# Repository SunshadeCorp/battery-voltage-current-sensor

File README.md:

# battery-voltage-current-sensor
Sensor Board for a voltage and current measurement

D1 Mini ESP8266 Microcontroller

Umax: 750VDC

Imax: +-50A 

Integrated supply voltage generation from the highvoltage source

2x temperature sensors onboard for system monitoring and overload protection

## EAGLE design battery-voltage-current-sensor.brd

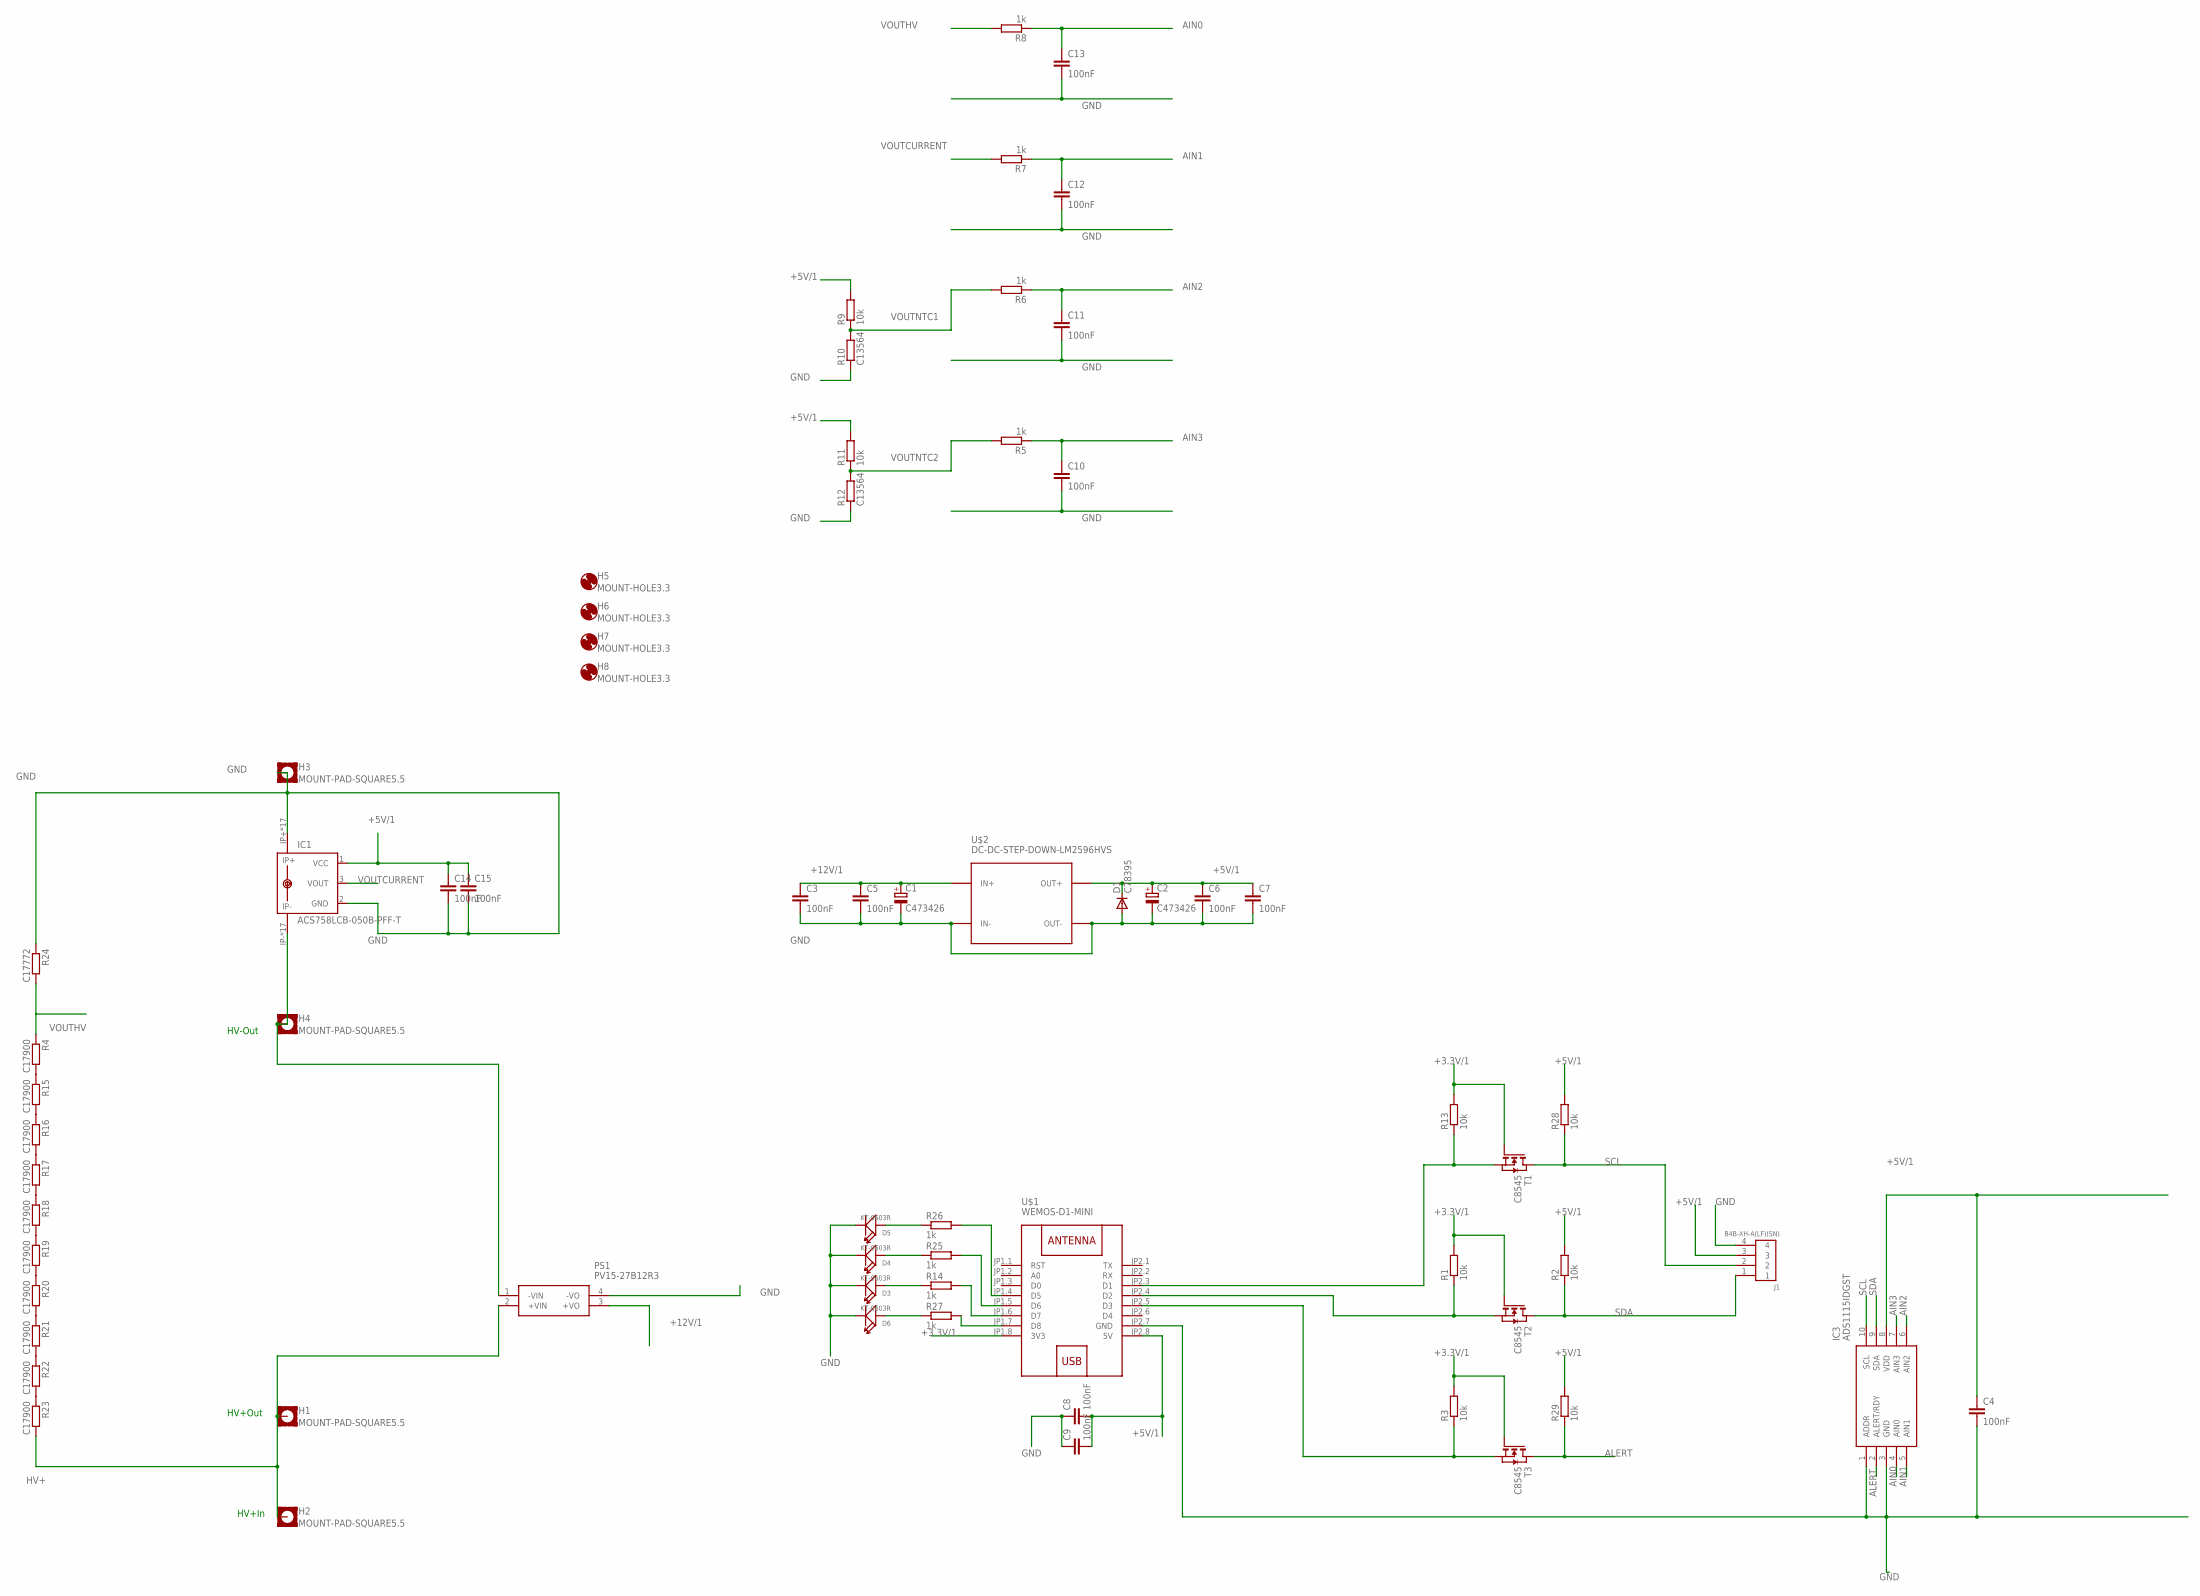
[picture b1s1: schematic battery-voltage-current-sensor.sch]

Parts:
C1, C2: C473426; UD-6,3X7,7_NICHICON
C3, C5, C6, C7, C8, C9, C10, C11, C12, C13, C14, C15: 100nF; C0603
C4: 100nF; C0805
D1: C78395; SMB
D3, D4, D5, D6: KT-0603R; LED-0603
H1, H2, H3, H4: MOUNT-PAD-SQUARE5.5; 5,5-PAD-SQUARE
H5, H6, H7, H8: MOUNT-HOLE3.3; 3,3
IC1: ACS758LCB-050B-PFF-T; CB-PFF
IC3: ADS1115IDGST; SOP50P490X110-10N
J1: B4B-XH-A(LF)(SN)
PS1: PV15-27B12R3; PV1527B12R3
R1, R2, R3, R9, R11, R13, R28, R29: 10k; R0603
R4, R15, R16, R17, R18, R19, R20, R21, R22, R23: C17900; R1206
R5, R6, R7, R8, R14, R25, R26, R27: 1k; R0805
R10, R12: C13564; R0603
R24: C17772; R0805
T1, T2, T3: C8545; SOT-23
U$1: WEMOS-D1-MINI
U$2: DC-DC-STEP-DOWN-LM2596HVS

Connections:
+3.3V/1: R1.2, R3.2, R13.2, T1.3 (G), T2.3 (G), T3.3 (G), U$1.JP1.8 (3V3)
+5V/1: C2.+, C4.1, C6.1, C7.1, C8.2, C9.2, C14.1, C15.1, D1.C, IC1.1 (VCC), IC3.8 (VDD), J1.3, R2.2, R9.2, R11.2, R28.2, R29.2, U$1.JP2.8 (5V), U$2.OUT+
+12V/1: C1.+, C3.1, C5.1, PS1.3 (+VO), U$2.IN+
AIN0: C13.1, IC3.4 (AIN0), R8.1
AIN1: C12.1, IC3.5 (AIN1), R7.1
AIN2: C11.1, IC3.6 (AIN2), R6.1
AIN3: C10.1, IC3.7 (AIN3), R5.1
ALERT: IC3.2 (ALERT/RDY), R29.1, T3.1 (D)
GND: C1.-, C2.-, C3.2, C4.2, C5.2, C6.2, C7.2, C8.1, C9.1, C10.2, C11.2, C12.2, C13.2, C14.2, C15.2, D1.A, D3.-, D4.-, D5.-, D6.-, H3.B5,5, IC1.2 (GND), IC1.IP+, IC1.IP+@2 (IP+), IC1.IP+@3 (IP+), IC1.IP+@4 (IP+), IC1.IP+@5 (IP+), IC1.IP+@6 (IP+), IC1.IP+@7 (IP+), IC1.IP+@8 (IP+), IC1.IP+@9 (IP+), IC1.IP+@10 (IP+), IC1.IP+@11 (IP+), IC1.IP+@12 (IP+), IC1.IP+@13 (IP+), IC1.IP+@14 (IP+), IC1.IP+@15 (IP+), IC1.IP+@16 (IP+), IC1.IP+@17 (IP+), IC3.1 (ADDR), IC3.3 (GND), J1.4, PS1.4 (-VO), R10.1, R12.1, R24.1, U$1.JP2.7 (GND), U$2.IN-, U$2.OUT-
HV+: H1.B5,5, H2.B5,5, PS1.2 (+VIN), R23.2
HV-: H4.B5,5, IC1.IP-, IC1.IP-@2 (IP-), IC1.IP-@3 (IP-), IC1.IP-@4 (IP-), IC1.IP-@5 (IP-), IC1.IP-@6 (IP-), IC1.IP-@7 (IP-), IC1.IP-@8 (IP-), IC1.IP-@9 (IP-), IC1.IP-@10 (IP-), IC1.IP-@11 (IP-), IC1.IP-@12 (IP-), IC1.IP-@13 (IP-), IC1.IP-@14 (IP-), IC1.IP-@15 (IP-), IC1.IP-@16 (IP-), IC1.IP-@17 (IP-), PS1.1 (-VIN)
unnamed: R1.1, T2.2 (S), U$1.JP2.4 (D2)
unnamed: R13.1, T1.2 (S), U$1.JP2.3 (D1)
unnamed: D3.+, R14.1
unnamed: R3.1, T3.2 (S), U$1.JP2.5 (D3)
unnamed: D4.+, R25.1
unnamed: D5.+, R26.1
unnamed: R4.2, R15.1
unnamed: R15.2, R16.1
unnamed: R16.2, R17.1
unnamed: R17.2, R18.1
unnamed: R18.2, R19.1
unnamed: R19.2, R20.1
unnamed: R20.2, R21.1
unnamed: R21.2, R22.1
unnamed: R22.2, R23.1
unnamed: D6.+, R27.1
unnamed: R27.2, U$1.JP1.7 (D8)
unnamed: R14.2, U$1.JP1.6 (D7)
unnamed: R25.2, U$1.JP1.5 (D6)
unnamed: R26.2, U$1.JP1.4 (D5)
SCL: IC3.10 (SCL), J1.2, R28.1, T1.1 (D)
SDA: IC3.9 (SDA), J1.1, R2.1, T2.1 (D)
VOUTCURRENT: IC1.3 (VOUT), R7.2
VOUTHV: R4.1, R8.2, R24.2
VOUTNTC1: R6.2, R9.1, R10.2
VOUTNTC2: R5.2, R11.1, R12.2

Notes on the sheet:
HV+In
HV+Out
HV-Out

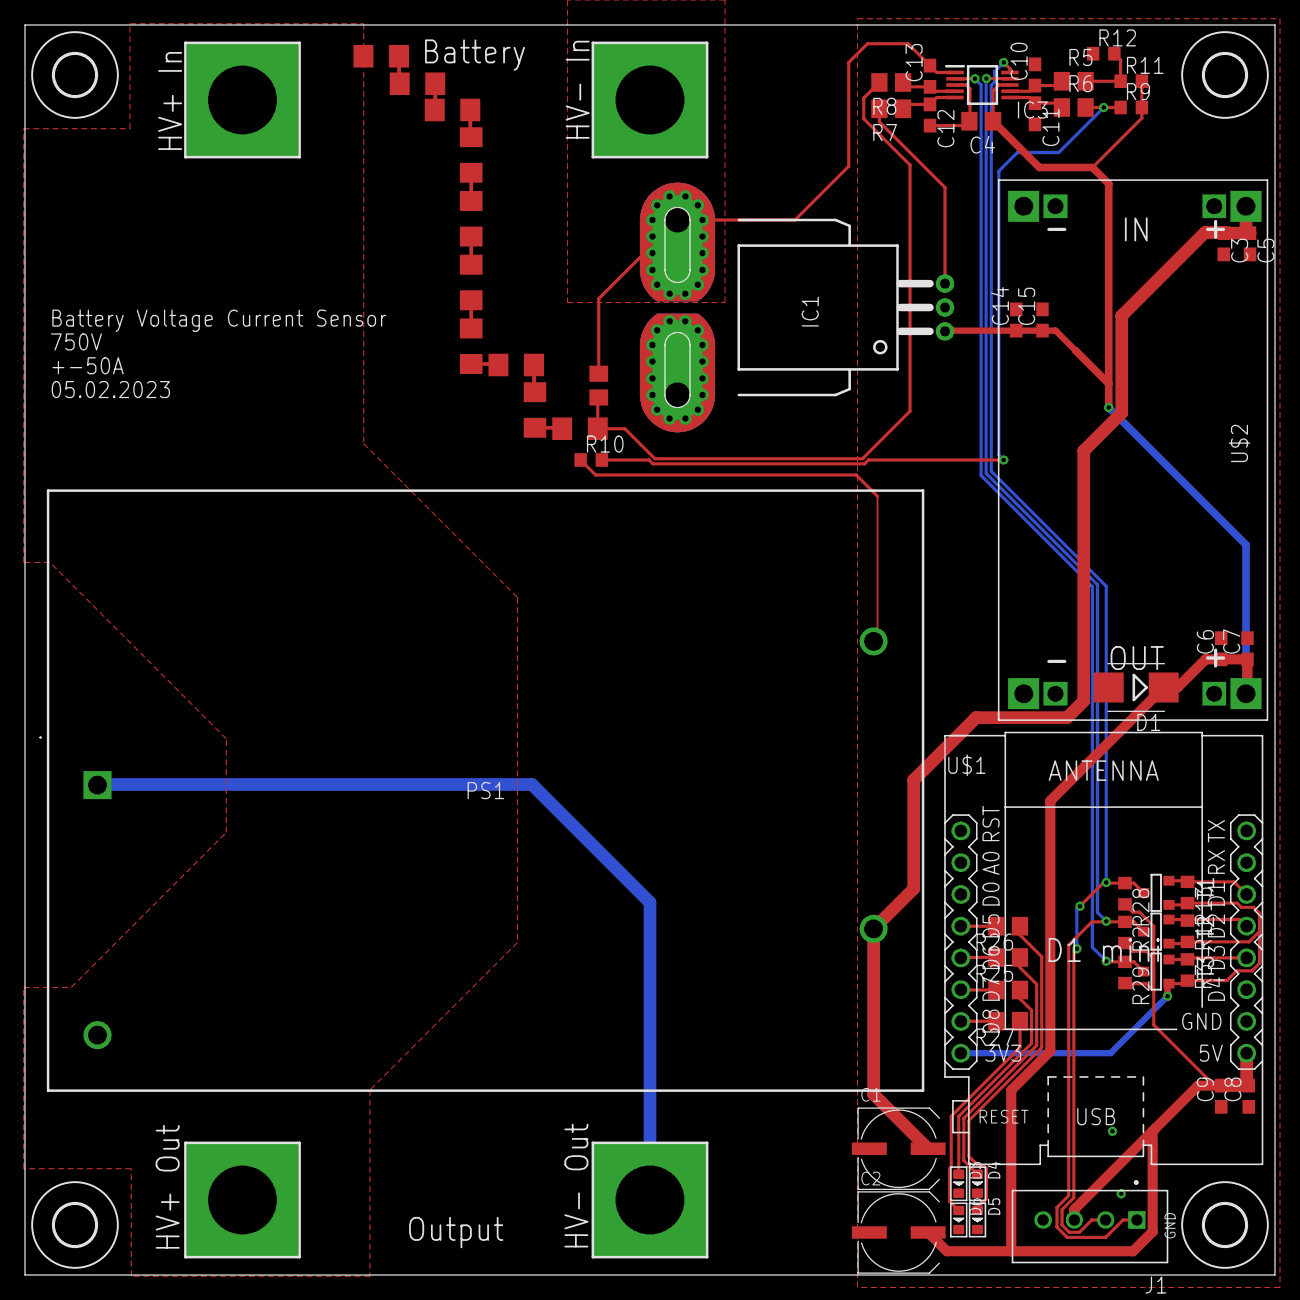
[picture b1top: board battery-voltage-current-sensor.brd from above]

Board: 2 copper layers, 100.0 x 100.0 mm, 66 parts (0 on the bottom side), 37 nets.

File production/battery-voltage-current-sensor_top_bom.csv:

Comment,Designator,Footprint,LCSC Part #
1k,R5 R6 R7 R8 R14 R25 R26 R27,R0805,
10k,R1 R2 R3 R9 R11 R13 R28 R29,R0603,
100nF,C3,C0603,
100nF,C4,C0805,
100nF,C5 C6 C7 C8 C9 C10 C11 C12 C13 C14 C15,C0603,
ADS1115IDGST,IC3,SOP50P490X110-10N,
C8545,T1 T2 T3,SOT-23,
C13564,R10 R12,R0603,
C17772,R24,R0805,
C17900,R4 R15 R16 R17 R18 R19 R20 R21 R22 R23,R1206,
C78395,D1,SMB,
C473426,C1,UD-6 3X7 7_NICHICON,
C473426,C2,UD-6 3X7 7_NICHICON,
KT-0603R,D3 D4 D5 D6,LED-0603,

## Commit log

2023-01-19 inital commit
2023-01-19 git ignore created
2023-01-19 DCDC added
2023-01-19 basic board and holes added
2023-01-19 mounting holes added
2023-01-20 first placing check
2023-01-21 DCDC as a module added
2023-01-21 first placing succes
2023-01-22 level shifter added
2023-01-22 first draft of production data generated
2023-01-22 external 12V added
2023-01-22 documentation folder and images added
2023-01-22 text added
2023-01-22 capacitors moved
2023-01-22 marking for 12 connector added
2023-01-22 3D step added
2023-01-23 ready to manufacture, ordered
2023-01-23 documentation images added
2023-02-01 documentation images edited
2023-02-01 software base project added
2023-02-01 folder moved
2023-02-03 basic software added
2023-02-03 autoformat
2023-02-03 fix build
2023-02-03 some SerialPrintsremoved, debug over mqtt
2023-02-04 unused variables removed
2023-02-04 voltage measurement resistors changed to 100k
2023-02-05 1000V DCDC position corrected
2023-02-05 current offset at start calibrated
2023-02-05 3d model updated
2023-02-05 Update README.md
    12V source removed, it is dangerous
2023-02-05 new topics, mqtt username and password, 78880 baud, delay 500
2023-02-13 error fixed
2023-02-13 connector swapped against a 4pin for a display
2023-02-13 connector rotated, ready to manufacture, ordered
2023-02-18 updated .gitignore + added version submodule
2023-02-18 reformat main.cpp
2023-02-18 current offset + ota + restart + blink
2023-03-01 updated 3D model
2023-03-13 new voltage factor

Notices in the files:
parts and their libraries:
diy-modules: Released under the Creative Commons Attribution 4.0 International License: http://creativecommons.org/licenses/by/4.0
